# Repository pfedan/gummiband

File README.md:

# Gummiband

Gummiband is a topological ("rubber band") autorouter for KiCad. It plans every connection as a
topology first (which side of which pad, via or locked track it passes) and only then turns the
plan into geometry: tight any-angle tracks with real arcs, pulled taut around the obstacles like
rubber bands between the pins. The router is written in Rust, uses every core of your machine and
comes as a KiCad plugin, a command line tool and an MCP server for AI agents.

What you keep is yours: everything you lock in KiCad (power lanes, a converter layout from the
datasheet, critical pairs) stays untouched and the router works around it.

Status: early development. Results route almost everything on real boards but still need a KiCad
DRC pass and some hand finishing. See the [milestones](docs/MILESTONES.md).

## Requirements

- KiCad 9 or 10 board files. The plugin needs KiCad 10 with the IPC API enabled.
- A Rust toolchain (edition 2024, so Rust 1.85 or newer): <https://rustup.rs>.
- Optional: `kicad-cli` (ships with KiCad) for DRC runs from scripts and the MCP server,
  `rsvg-convert` (librsvg) and ImageMagick for renders and animations.

## Setup

Build the router once:

```bash
git clone https://github.com/pfedan/gummiband
cd gummiband
cargo build --release
# binary: target/release/gummiband
```

Then pick how you want to use it:

- **KiCad plugin** (recommended): link the `plugin/` folder into KiCad's IPC plugin directory,
  enable *Preferences > Plugins > Enable KiCad API*, and tell the plugin where the binary is
  (`plugin/settings.json`, copied from `settings.example.json`). Step by step in the
  [installation guide](docs/guide/installation.md).
- **Command line**: use `target/release/gummiband` directly, see below.
- **AI agents**: `cargo build --release -p gummiband-mcp` builds the MCP server, see
  [Working with an AI agent](docs/guide/ai-agents.md) and the reference in [docs/MCP.md](docs/MCP.md).

## Quickstart

### In KiCad

1. Optional, for a board whose parts are not placed yet: lock the connectors and whatever else
   has its spot, click *Place with Gummiband* and pick which parts move (new, not yet tested
   live in KiCad).
2. Lock the copper you want to keep (select, right click, *Locking > Lock*).
3. Click *Route with Gummiband* in the PCB editor's plugin toolbar.
4. Leave the defaults (keep locked copper, 14 runs, via cost 3.0, 3 geometry
   generations) and press OK. A window shows the phase, the generation, the routed connections,
   vias, length and remaining violations. The result keeps improving until you press *Accept
   current result*; the window tells you when the search has settled.
5. Look at the result. It arrives as one undo step, so Ctrl/Cmd+Z takes it back entirely.
6. Refill zones (B) and run the DRC. Fix or reroute what is left by hand, then save.

Your board file on disk is not touched until you save.

### On the command line

```bash
# what the router sees: layers, planes, nets, net classes, rules
target/release/gummiband info my_board.kicad_pcb

# optional: place the parts that are not locked or mechanical, into a new file
target/release/gummiband place my_board.kicad_pcb -o my_board.placed.kicad_pcb

# route it (or the placed file), keep locked tracks and vias, write a new file next to it
target/release/gummiband route my_board.kicad_pcb -o my_board.routed.kicad_pcb --scope keep_locked

# judge the result with KiCad
kicad-cli pcb drc --refill-zones --format json -o drc.json my_board.routed.kicad_pcb
```

The `.kicad_pro` (net classes) and `.kicad_dru` (custom rules) next to the board are read
automatically. Copy them next to the output before running the DRC on it.

## Documentation

The user guide lives in [docs/guide](docs/guide/README.md):

- [A tour of the features](docs/guide/tour.md): what Gummiband does, one picture per feature.
- [Installation](docs/guide/installation.md): binary, plugin, optional tools, troubleshooting.
- [Placing and routing in KiCad](docs/guide/kicad-plugin.md): the plugin dialogs and what each
  option does.
- [Command line](docs/guide/cli.md): every command and option, the output and the JSON report.
- [Working with an AI agent](docs/guide/ai-agents.md): setup of the MCP server and a session
  from netlist to DRC, with the power and reference plane checks.
- [Workflows](docs/guide/workflows.md): locking power lanes, routing by priority, judging results,
  placing parts, movable parts, placement variants, animations.
- [How Gummiband routes](docs/guide/concepts.md): what the router respects, how it decides, and
  what it does not do yet.
- [Benchmarks](docs/guide/benchmarks.md): the synthetic suite and the real boards.

Reference and development:

- [docs/MCP.md](docs/MCP.md): the MCP server for AI agents, tools and client setup.
- [docs/ARCHITECTURE.md](docs/ARCHITECTURE.md): crates, data model, algorithms.
- [docs/MILESTONES.md](docs/MILESTONES.md): what is done and what comes next.
- [docs/DECISIONS.md](docs/DECISIONS.md): standing decisions and working rules of the project.
- [docs/ENVIRONMENT.md](docs/ENVIRONMENT.md): the `GB_*` environment variables for development
  and measurements (logs, switches, experiment knobs); not a stable interface.
- [plugin/README.md](plugin/README.md): plugin internals, dry runs and tests.
- [bench/README.md](bench/README.md): the benchmark scripts.

## License

All rights reserved. Gummiband is not published under an open source license; ask the author
before using it beyond trying it out.

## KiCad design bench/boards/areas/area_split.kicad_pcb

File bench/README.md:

# Benchmarks

## Synthetic suite

`gen_boards.py` (plain Python 3) writes small KiCad 10 boards of increasing difficulty into
`boards/`, each as `<name>.kicad_pcb` plus `<name>.kicad_pro` (net classes, rules). The boards are
deterministic (fixed seeds, UUIDs derived from the board name); rerun the generator after changing
it and commit the boards together with it. Every unrouted board passes `kicad-cli pcb drc` with
only unconnected items.

| Board | Layers | What it tests |
| --- | --- | --- |
| `easy` | 2 | a few 2 pin connections between 0603 parts |
| `medium` | 2 | SOIC-14, SOT-23 and 0603 parts, random local netlist, an 8 pin GND net |
| `bus` | 2 | 16 bit bus between two 0.5 mm FPC connectors with a 90 degree turn, GND across the bus, 45 degree parts in the bend |
| `power_mix` | 2 | 1 mm (VIN, GND) and 0.75 mm (VOUT) nets with 0.2 mm signals through a 3.5 mm channel between two THT walls |
| `crossing` | 2 | two 1 mm pitch SMD connectors with reversed pin order |
| `qfn_fanout` | 4 (In1 GND, In2 3V3 planes) | QFN-48 at 0.5 mm to a ring of 40 pull resistors, plane fan-out vias |
| `four_signal_layers` | 4 signal | dense random netlist around two QFN-32 and two SOIC-14 |
| `bga_escape` | 4 (planes) | 8x8 BGA at 0.8 mm, 48 signals escape to four edge connectors, 0.1/0.1 mm rules |
| `bga_dense` | 4 (planes) | 10x10 BGA at 0.8 mm, 3 signal rings (84 signals): the inner ring needs vias on 2 signal layers |
| `fine_pitch` | 2 | QFN-56 at 0.4 mm with 0.2/0.19 mm rules, nets in pin order: a clean straight fan-out |
| `fine_pitch_mixed` | 2 | the same part with shuffled nets: vias and crossings right at the pins, the Corne problem in small |
| `diff_pairs` | 2 | 8 differential pairs (`_P`, `_N`) with a ground between them, 0.5 mm connectors at an angle, parts in the way |
| `matching` | 2 | a byte lane and a clock pair between two 0.5 mm connectors at an angle, with `length`, `skew` and `diff_pair_uncoupled` rules |
| `pair_wall` | 2 | a USB pair through the one gap of a wall of THT pins (the gap takes the wide pair or three single tracks, between the pins only one single track fits), six short nets across the wall next to the gap |
| `pair_traffic` | 2 | two long pairs from a connector to a QFN-32 across a field of 0603 parts with random local nets |
| `parts_easy` | 2 | part to part, level 1: QFN-32 and SPI flash with a planar bus, series resistors to a header |
| `parts_medium` | 2 | level 2: SPI flash in its real pinout (bus on both sides of the flash), I2C sensor with pull-ups and an interrupt, 6 bit bus with one swap, random local nets |
| `parts_hard` | 2 | level 3: QFN-48 with shared SPI to two devices, shared I2C with pull-ups to two more, 8 bit bus with two swaps to an edge connector, USB pair, random local nets |
| `parts_multi` | 4 (planes) | level 4: MCU (QFN-48) and PHY (QFN-32) with a 12 net bus with swaps, SPI flash, 6 bit latch bus, I2C shared by both chips with pull-ups, three pairs, a debug header wired to both, random local nets |
| `parts_multi_feed` | 4 (planes) | level 5: `parts_multi` with 40 scattered 0603 parts (chicken feed), half of them with a plane via |
| `parts_xhard` | 4 (planes) | extra hard: `parts_multi_feed` on a board 25 % smaller in each direction (positions scaled, edge connectors at their edge, overlaps spread apart) |

`run_suite.sh [board ...]` builds the CLI, routes every board into `boards/out/`
one board after another (`--runs 4 --generations 1 --geometry-generations 0` with `RAYON_NUM_THREADS=4`, override with
`RUNS`, `GENERATIONS`, `GEOMETRY_GENERATIONS`, `RAYON_NUM_THREADS`, `ROUTE_ARGS`, `TIMEOUT`), runs
`kicad-cli pcb drc --refill-zones` on each result (next to a copy of the board's `.kicad_pro`) and
prints a table: connections routed, vias, length, router wall time, Gummiband's own clearance
check, and the KiCad DRC counts (unconnected, clearance, shorts, crossings, other; silk and lib
types ignored). A crash or timeout on one board is reported in the table and the notes and does
not stop the suite. The table is also written to `boards/out/results.txt`; the router output of
each board is in `boards/out/<board>.route.log`.

## Route hashes (regression test)

`hashes.sh` routes the synthetic boards with fixed settings and prints one line per run: the name
and the SHA-1 of the routed `.kicad_pcb`. Runs without an open end are deterministic (same input
and seed, any thread count), so the list is a regression test: a refactoring or a
micro-optimisation must leave it unchanged. Only the router runs, no `kicad-cli` is needed.

The reference holds for every build. The router used to call `sin`, `cos`, `atan2`, `acos`, `exp`,
`log`, `pow` and `hypot` of the system's maths library, whose last bits differ between glibc
versions, musl and macOS: the first CI run (glibc of Ubuntu 26.04) changed 12 of 15 hashes of a
reference made with glibc 2.39, with the same compiler. Since 2026-11-10 these functions come from
`gummiband_core::math` (the `libm` crate, pure Rust, compiled in), and the binary asks the system's
maths library for nothing. Measured on x86_64 Linux: the glibc build and the static musl build give
the same hash on all 27 runs, where before they agreed on 6. The reference did not change with it:
the hashes are the ones the musl build had before. (The crate is a port of musl's maths library; its
`sin`, `cos`, `tan`, `atan2`, `acos` and `hypot` give the bits of today's musl, its `exp`, `ln` and
`powf` are an older version and differ in some last bits, which no run of the list noticed.) Another
processor (macOS on ARM) is expected to give the same hashes, because only operations that IEEE 754
fixes to the last bit are left to the hardware; that is not measured yet. `cargo test -p
gummiband-core math` compares the bits of every function with fixed numbers, on any machine.

```sh
cargo build --release -p gummiband-cli
bench/hashes.sh --check             # all boards against hashes.txt, about 2 min at 4 threads
QUICK=1 bench/hashes.sh --check     # the quick set against hashes.quick.txt, what CI runs

# two binaries against each other: the build before a change and the one after it, or two
# builds of the same source (glibc and musl, two compilers)
bench/hashes.sh --compare path/to/old/gummiband target/release/gummiband
QUICK=1 bench/hashes.sh --compare OLD NEW

bench/hashes.sh easy bus            # print the hashes of some boards, compare nothing
```

Every board is routed with `--runs 4 --generations 1 --geometry-generations 0 --no-move-parts`.
A few extra runs on small boards cover option paths the plain run does not touch (the defaults,
`--angles 45`, `--pairs band`, `--pairs pull`, `--patterns groups`, `--negotiate`); their names carry a
`+`, as in `medium+45`. `--check` prints a diff and exits with 1 when a hash differs, and a run
that fails shows up as `FAILED` in place of its hash. `RAYON_NUM_THREADS` sets the threads
(default 4) and changes the time only.

A change that is meant to alter results (a new heuristic, a changed default) is judged with
`compare.py` and the KiCad DRC as before, and then the reference is updated deliberately, in the
same commit as the change and with the reason in its message:

```sh
bench/hashes.sh --update            # rewrites hashes.txt
QUICK=1 bench/hashes.sh --update    # rewrites hashes.quick.txt
```

Never update the reference to make a refactoring pass: there a changed hash is a bug. A new board
from `gen_boards.py` needs `--update` too, since the full list covers every board in `boards/`.
The boards for areas in `boards/areas/` are in neither list, see below.

## Areas: pours and planes

`gen_boards.py` also writes five small boards into `boards/areas/`, each with one situation of a
pour or a plane. They are fixtures for the fill model behind `gummiband areas` (what the copper
fill of a net with a zone reaches), not routing problems: each routes in under a second.

| Board | Layers | What it holds | What the fill model says |
| --- | --- | --- | --- |
| `area_strips` | 2 | a GND pour on both layers (minimum width 0.2 mm, clearance 0.2 mm); six pens of locked track around one GND pad each, open only through a channel 4 mm long that leaves a strip of fill 0.10, 0.15, 0.20, 0.25, 0.30 or 0.40 mm wide | the pads behind 0.10 and 0.15 mm sit on islands (one via site each), the others are reached, as in KiCad; the pad behind 0.20 mm is doubtful |
| `area_island` | 2 | a GND pour on both layers; locked tracks from edge to edge cut the front into a region and a band with one GND pad each, strips of fill 0.21 mm wide between them that hold nothing, and the rest with a through hole pin; one GND pad stands in a pen of track that cuts its four spokes | the region and the band are islands with a via site each; the pad in the pen has no spoke; the strips are left out. Routed with `--areas fill --keep-locked`: two vias, one piece of track, all six pads reached (`area_route.rs`) |
| `area_halves` | 2 | GND parts at the left, GNDR parts at the right, three signals across, no zone; `area_halves.nets.json` leaves the two nets out of a route | a pour of both nets gives each a zone per layer around its own pads; no spot lies in two zones; all 6 pads of each are reached |
| `area_far` | 2 | VBUS with an area on B.Cu over the right third of the board, two through hole pins in it, six pins outside it | 2 of 8 pads reached; the farthest pad is 28.0 mm from a spot where a via lands in the area |
| `area_split` | 4 (In1 GND, In2 split) | In2.Cu holds +3V3 at the left and +5V at the right, 0.6 mm between the outlines; each net has one SMD pin over the other half and one through hole pin in it | each half reaches its two through hole pins; the pin in the other half lies outside the outline |

`cargo test -p gummiband-app --test area_boards` holds the model to the last column. The boards
are **not in the hash lists**: `hashes.sh` lists the boards of `boards/` only. They are quick
and their routed files are the same from run to run, but the hash of a routed file does not see
what they are for, the fill, and a board in the lists costs a reference line that every change
of the router has to carry.

`boards/areas/kicad/` holds four routed boards of the suite with a GND pour on both layers,
as KiCad 10 got them from the loop below (`<board>.s<seed>`). They are kept because the model
and KiCad disagreed on them; the tests in `area_boards.rs` pin KiCad's answer on each. They are
not written by `gen_boards.py` and must not be routed again: a new route is a new board that
KiCad has not seen.

### The model against KiCad's fill

The model was held against KiCad's fill on the planes of the LED controller, and against
KiCad 10 on the boards below (see "What KiCad 10 said"). To repeat it on a machine with
`kicad-cli` (KiCad 9 or 10) on the PATH:

```sh
python3 bench/gen_boards.py          # only if bench/boards/areas is missing
bench/areas-kicad.sh                 # the four boards above
```

and, for thin strips as a router leaves them, ten boards of the suite routed without GND, with
a pour of GND on both layers and one via per island:

```sh
for seed in 1 2 3; do
    POUR=GND:F.Cu,B.Cu \
    ROUTE_ARGS="--runs 4 --generations 1 --geometry-generations 0 --no-move-parts --seed $seed" \
    bench/areas-kicad.sh bench/boards/bus.kicad_pcb bench/boards/diff_pairs.kicad_pcb \
        bench/boards/fine_pitch.kicad_pcb bench/boards/fine_pitch_mixed.kicad_pcb \
        bench/boards/matching.kicad_pcb bench/boards/medium.kicad_pcb \
        bench/boards/parts_easy.kicad_pcb bench/boards/parts_hard.kicad_pcb \
        bench/boards/parts_medium.kicad_pcb bench/boards/power_mix.kicad_pcb
    cp bench/boards/out/areas/results.txt bench/boards/out/areas/results.seed$seed.txt
done
```

`areas-kicad.sh` routes a board (and pours it where asked), lets KiCad refill a copy
(`kicad-cli pcb drc --refill-zones --save-board`) and runs `gummiband areas --json` on that
copy, so that the model and KiCad's fill are compared on the same copper. It prints one line per
net and layer, also into `boards/out/areas/results.txt`:

- `mm2 model only / file only`: fill only one of the two has, beyond what the raster explains;
- `pads m/f`: pads only the model's fill touches, and pads only KiCad's fill touches;
- `unconn model/kicad`: the unconnected items the model expects for the net, and those KiCad's
  DRC counts;
- `doubtful`: the pads whose answer changes within one raster cell.

The model holds on a board where both pad lists are empty and the two unconnected counts agree.
A pad in `pads m/f` that is not in the doubtful list is a finding: send the line and the two
files `<name>.areas.json` and `<name>.filled/<name>.kicad_pcb`. On `area_halves` the question
is also whether KiCad reads the outlines as written (a region enclosed by another is cut into
its outline through a slit; this board has none, a board with an island of the other ground
has).

#### What KiCad 10 said

Measured 2026-11-11 with `kicad-cli` 10 and the commands above (the four area boards of that
day, the ten boards with seeds 1 to 3). Where the two disagreed the model now follows KiCad, and a test
pins KiCad's answer on the board where it showed:

| Where | The model said | KiCad 10 | Now |
| --- | --- | --- | --- |
| `area_strips` | the strip of 0.20 mm, the minimum width itself, is shut: 4 pieces on the front, 3 unconnected, `TP3.1` doubtful | passes it: 3 pieces, 2 unconnected | a cell centre at just the clearance is fill, the strip passes; `TP3.1` stays doubtful |
| `fine_pitch_mixed` seed 2, `R50.2` to `R54.2` and `R56.2` (a row at a pitch of 1.6 mm) | none of their spokes ends in fill: 7 unconnected | joins all six: 1 unconnected | a spoke also stays where it and a spoke of another pad hold each other's ends: 1 unconnected (`U1.57`) |
| `fine_pitch_mixed` seed 3, `U1.57` (exposed pad) | an island, 1 piece of fill on the front | unconnected too, but 2 pieces | the spokes are laid and tested as KiCad lays them: the island is a piece of 1 mm2 that stays, 2 pieces |
| `matching` seed 3, `J1.16` | no spoke ends in fill, and not doubtful | joins it | still not reached, but doubtful: the end of its one free spoke lies 0.05 mm from the clearance of a track, one cell outside the fill at the raster as it is, inside with half a cell less |
| `parts_medium` (all seeds), `fine_pitch_mixed` seeds 1 and 3, back layer | nothing of GND holds the pour there: every piece left out, 0 mm2 | keeps all of it (1393 to 1760 mm2 in 1 or 35 to 41 pieces) and warns of isolated copper for each | the pieces stay in the model and the report says so (`isolated`). `ground_pour` and `pour_stitch` still write the zone of such a layer: not writing it is open |
| `parts_medium`, `U2.4` | reached, doubtful | unconnected | as before: this is what doubtful is for |
| `area_halves`, `area_far`, `area_split` | | no difference at any pad, no DRC item; the model has 0.4 to 5 mm2 more fill of 344 to 1375 | as before |

What is assumed about KiCad's filler and not measured case by case: the end of a spoke lies the
thermal gap, half the minimum width and 0.005 mm beyond the box of the pad; a spoke is as wide
as the spoke width or the short side of the pad and is left out where that is under the minimum
width; it stays when its end lies in the fill as it is after the minimum width took its part,
or when it and a spoke of another pad hold each other's ends; other copper then cuts it by its
clearance. A pad whose answer hangs on this within a raster cell is named as doubtful.

On `J1.16` the two are not reconciled. Read from the copper, its spoke ends in a pocket of fill
of about 0.2 mm2 between the tracks of DQ4 and DQ0, which lie 0.16 mm apart where the pocket
would have to open: the pad would hang on that pocket and on nothing else. If KiCad calls the
pad connected, something in this reading is wrong; the filled board at 105.5, 114.7 shows what.

### `areas tracks` against `areas fill`

`areas-route.py` routes a board both ways with the same binary, `--areas tracks` (a net with a
pour is laid as tracks) and `--areas fill` (the other nets first, then only what the fill does
not reach), and prints one line per board, seed and mode: connections, the pads of the area
nets that the router's fill model leaves open on the routed board with its pour, the pieces
and spots of the own clearance check, vias, length, CPU seconds, and the seconds the fill model
took inside the search (summed over the threads) with the number of its runs. It needs no KiCad:

```sh
cargo build --release -p gummiband-cli
bench/areas-route.py                 # ten boards of the suite with GND poured, the four area boards
bench/areas-route.py /path/to/board.kicad_pcb=GND      # another board, GND poured on F.Cu and B.Cu
bench/areas-route.py /path/to/board.kicad_pcb          # the zones of the file are the areas
```

The table is also written to `boards/out/areas-route/results.txt` (and `results.json`); the
routed boards are deleted unless `--keep` is given. `--fill-args=--no-area-stitch` routes the
fill runs without the vias for islands, and `GB_AREA_ESCAPE=0` in the environment without the
price at the pads of the area nets.
`--modes fill` routes one mode only. Write `--args=...` and `--fill-args=...` with the equals
sign: their values begin with a dash.

Measured without KiCad (2026-11-14, commit 5d63666 of `claude/geometry`, the settings of the
suite: `--runs 4 --generations 1 --geometry-generations 1 --no-move-parts`). Every number is
the sum of the seeds 1, 2 and 3; `open pads` is the router's own model, not KiCad.

| board | mode | routed | open pads | pieces/spots | vias | of them island vias | mm | cpu s | model s (runs) |
| --- | --- | ---: | ---: | ---: | ---: | ---: | ---: | ---: | ---: |
| `bus` | tracks | 66/66 | 0 | 0/0 | 60 | 0 | 1911 | 41 |  |
| `bus` | fill | 66/66 | 0 | 0/0 | 50 | 8 | 1933 | 43 | 7 (27) |
| `diff_pairs` | tracks | 93/93 | 0 | 0/0 | 90 | 0 | 2916 | 53 |  |
| `diff_pairs` | fill | 93/93 | 0 | 2/2 | 126 | 0 | 2925 | 96 | 11 (36) |
| `fine_pitch` | tracks | 336/336 | 0 | 0/0 | 6 | 0 | 2304 | 18 |  |
| `fine_pitch` | fill | 336/336 | 0 | 0/0 | 6 | 6 | 1928 | 29 | 6 (24) |
| `fine_pitch_mixed` | tracks | 336/336 | 0 | 28/5 | 368 | 0 | 4509 | 393 |  |
| `fine_pitch_mixed` | fill | 335/336 | 0 | 1/1 | 426 | 0 | 4211 | 624 | 44 (157) |
| `matching` | tracks | 78/78 | 0 | 0/0 | 102 | 0 | 1800 | 66 |  |
| `matching` | fill | 78/78 | 0 | 0/0 | 18 | 6 | 1572 | 191 | 8 (27) |
| `medium` | tracks | 114/114 | 0 | 0/0 | 36 | 0 | 1347 | 7 |  |
| `medium` | fill | 114/114 | 0 | 0/0 | 42 | 6 | 1137 | 15 | 6 (27) |
| `parts_easy` | tracks | 66/66 | 0 | 0/0 | 15 | 0 | 450 | 2 |  |
| `parts_easy` | fill | 66/66 | 0 | 0/0 | 3 | 0 | 393 | 8 | 4 (27) |
| `parts_hard` | tracks | 225/225 | 0 | 0/0 | 172 | 0 | 3260 | 16 |  |
| `parts_hard` | fill | 225/225 | 0 | 0/0 | 162 | 18 | 2802 | 45 | 13 (27) |
| `parts_medium` | tracks | 129/129 | 0 | 0/0 | 60 | 0 | 1545 | 9 |  |
| `parts_medium` | fill | 129/129 | 0 | 0/0 | 27 | 0 | 1560 | 21 | 10 (27) |
| `power_mix` | tracks | 57/57 | 0 | 0/0 | 17 | 0 | 960 | 7 |  |
| `power_mix` | fill | 57/57 | 0 | 0/0 | 15 | 0 | 657 | 12 | 8 (27) |
| **the ten** | tracks | 1500/1500 | 0 | 28/5 | 926 | 0 | 21002 | 612 |  |
| **the ten** | fill | 1499/1500 | 0 | 3/3 | 875 | 44 | 19118 | 1083 | 116 (406) |
| `area_strips` | tracks | 27/27 | 0 | 0/0 | 0 | 0 | 189 | 1 |  |
| `area_strips` | fill | 27/27 | 0 | 0/0 | 0 | 0 | 0 | 3 | 3 (24) |
| `area_far` | tracks | 60/60 | 0 | 0/0 | 0 | 0 | 654 | 2 |  |
| `area_far` | fill | 60/60 | 0 | 0/0 | 6 | 0 | 549 | 6 | 4 (27) |
| `area_split` | tracks | 51/51 | 0 | 0/0 | 36 | 0 | 399 | 2 |  |
| `area_split` | fill | 51/51 | 0 | 0/0 | 36 | 0 | 399 | 2 | 0 (0) |
| `area_halves` | tracks | 69/69 | 0 | 0/0 | 3 | 0 | 678 | 3 |  |
| `area_halves` | fill | 69/69 | 0 | 0/0 | 6 | 0 | 468 | 17 | 10 (27) |
| ledctl, its planes | tracks | 1042/1044 | 0 | 26/11 | 934 | 0 | 7366 | 363 |  |
| ledctl, its planes | fill | 1042/1044 | 0 | 26/11 | 934 | 0 | 7366 | 368 | 0 (0) |
| ledctl, GND poured | tracks | 1042/1044 | 0 | 26/11 | 934 | 0 | 7366 | 369 |  |
| ledctl, GND poured | fill | 1098/1098 | 0 | 3/3 | 945 | 8 | 8194 | 335 | 130 (56) |

In short, on the ten: `fill` lays 9 % less track and 6 % fewer vias than `tracks`, joins as
much (one connection of `fine_pitch_mixed` is lost to a short the last check takes out) and
takes 77 % more CPU time. The table of 2026-11-11 (commit 980246a) had 1047 vias for `tracks`
and 815 for `fill`: since then the routes of `tracks` got better by more vias than those of
`fill`.

What the table does not show:

- The two open connections of the LED controller with `tracks` are `BUCK_PG from R116.2` on
  the seeds 1 and 3: the small search of the suite settings leaves it open, the default
  settings of a route join it on every seed.
- On more seeds `fill` has open pads on `diff_pairs`: 3 on seed 4 and 2 on seed 7 (seeds 4 to
  7 measured on `fine_pitch_mixed`, `diff_pairs`, `bus` and `parts_hard`). GND has four pads
  there, the fill lies in 38 pieces, and the pads at the ends of the connectors have every
  spoke of their thermal relief cut and find no way to the piece that counts as the area. The
  step that lays open connections again on the finished copper does not help them.
- The three bullets below are of 2026-11-11 (commit 980246a) and were not measured again.
  At that commit the two open pads of the table were `J1.16` and `J2.16` of `matching` on
  seed 1 (pads with a thermal relief whose spokes end in no fill on the finished copper);
  `matching` joins everything now.
- A second run of the 42 lines with `fill` gave the same 42 lines.
- Without the vias for islands (`--fill-args=--no-area-stitch`, the ten boards): 18 open pads
  in 12 groups on 13 of the 30 runs, 877 vias, 19291 mm. Looked at on `parts_hard`: the
  search ended the track of `C2.2` in a piece of fill that hung on the area then and is an
  island on the finished copper; the last check takes such a track back. The via for an
  island is set on the finished copper and does not depend on what the search saw. This
  reading is in doubt since: the last check could also take a track back because it did not
  know the cells of the area (see `area_island`), which gives the same picture. Not measured
  again after that repair.
- Without the price at the pads (`GB_AREA_ESCAPE=0`, the ten boards): 13 open pads on 3 of the
  30 runs (`fine_pitch_mixed` 12, `diff_pairs` 1), 110 violating pieces at 24 spots against 6
  at 6, 780 vias, 19022 mm.
- The LED controller as it is has its planes on inner layers and no area on a routed layer:
  the files of `tracks` and `fill` are the same byte for byte. With GND poured on the outer
  layers as well (`ledctl.kicad_pcb=GND`) the route with `fill` counts 366 connections against
  348, because every group of pads of an area net counts and not only the pads that need a
  way to the plane.
- `model s` is wall time summed over the threads of the search. The machine was shared with
  another job, so it is an upper bound on the CPU time of the model.

**With KiCad** (`kicad-cli` of KiCad 9 or 10 on the PATH), `--kicad` lays the pour on every
result (the example `pour_stitch`: the zones, and one via per island that still has none), lets
KiCad refill it and adds three columns from KiCad's DRC: unconnected items (of the area nets /
of all nets), clearance violations, dangling vias and track ends. This is the judgement that
counts; the model's column `open pads` is what the router believed.

```sh
cargo build --release -p gummiband-cli --example pour_stitch
bench/areas-route.py --kicad --keep                    # the fourteen boards, three seeds each
```

The acceptance run on the Corne (`prepare-ext.sh` fetches and strips it into
`work/ext/corne/`), with the default settings of a route, three seeds:

```sh
bench/prepare-ext.sh
cargo build --release -p gummiband-cli --example pour_stitch
bench/areas-route.py --kicad --keep --args="" bench/work/ext/corne/corne.kicad_pcb=GND
```

`areas fill` passes when, on every seed and against the line of `tracks` ("route all, then
pour"): `unconn` of GND is 0; `clear` is no more than the 119 that the Corne had with GND left
out of the route; `vias` is no more than the 226 of that run plus the vias set for islands
(`areas: N vias set for islands of fill` in the log, `area_vias` in the report); `dangling` is
0. For the LED controller with a GND pour on the outer layers
(`bench/areas-route.py --kicad --keep --args="" /path/to/ledctl.kicad_pcb=GND`) nothing may be
worse than its line of `tracks`. With `--keep` the boards KiCad judged are
`boards/out/areas-route/<board>.s<seed>.<mode>.filled.kicad_pcb`, next to `.drc.json`; send
those two files for a pad that KiCad's DRC calls unconnected and the column `open pads` does
not count.

On the Corne with KiCad 10 (2026-11-11, before the two repairs named above) `fill` had more
clearance violations than `tracks` on every seed (573 against 439 over the seeds 1 to 3), most
of them at the two QFNs. Whether the price at the pads of the area nets pushes the signals
aside there is measured with the same seeds and the price off:

```sh
bench/areas-route.py --kicad --keep --modes fill --args="" bench/work/ext/corne/corne.kicad_pcb=GND
GB_AREA_ESCAPE=0 bench/areas-route.py --kicad --keep --modes fill --args="" bench/work/ext/corne/corne.kicad_pcb=GND
```

Compare `clear`, `unconn` and `vias` of the two tables line by line (the second run overwrites
`boards/out/areas-route/results.txt`: copy it first). Without KiCad the column `pieces/spots`
of the own clearance check stands in for `clear`. The price is not to be tuned on the small
boards alone: of the ten only `fine_pitch_mixed` and `diff_pairs` answer to it (see above). One
route of the Corne with the default settings takes more than an hour of CPU time.

## Two sided placement

`gen_two_sided.py` writes four synthetic boards into `boards/two_sided/` for `gummiband place
--two-sided` (placement only, no routing): `ts_som` (4 layers, 42 x 30 mm, BGA SoC and memory,
PMIC, about 120 0402 parts, a board to board connector locked on the back; the parts need about
1.4 times the front), `ts_sensor` (34 x 23 mm, a coin cell holder locked on the back, an antenna
keepout on the front: one sided nothing fits, two sided the front holds nearly all), `ts_roomy` (a
control with room to spare) and `ts_tht` (through hole electrolytics and a terminal block between
SMD converters). `check_sides.py PLACED [--input ORIGINAL]` checks a result from the file alone:
courtyard overlaps per side, the holes of through hole parts against parts on the other side, SMD
pads and courtyards on the layers of their side, mirrored texts on the back, and with `--input`
that every part that changed sides keeps its pad distances and is mirrored. `draw_sides.py PLACED
OUT.svg` draws front and back next to each other.

With `--iters 1000000`, one start, seed 1 (counts of 2026-11-10, with the maths of
`gummiband_core::math`; the system's maths gave 0 and 10 on `ts_sensor` and `ts_tht`):

| Board | One sided | Two sided: parts on the back | Wall time |
| --- | --- | --- | --- |
| `ts_som` | fails before the search, 321 mm2 missing | 105 | 20 s |
| `ts_sensor` | fails before the search, 275 mm2 missing | 1 (the front holds the rest once the holder only takes the back) | 6 s |
| `ts_roomy` | places | 9 (decoupling capacitors under their IC) | 3 s |
| `ts_tht` | places | 11, some under the electrolytics | 3 s |

`check_sides.py` finds no problem on any of them.

## LED controller

`prepare-ledctl.sh` strips the real LED controller board,
`run-ledctl.sh` routes it and prints the KiCad DRC summary; `drc_report.py` summarizes a
DRC JSON report in more detail.

## Relaxation on the CPU and the GPU

`cargo run --release -p gummiband-cli --features gpu --example relax_bench -- BOARD` routes the
board with a small search and relaxes the same routing on the CPU and the GPU. It prints the time,
the core seconds, a breakdown per round, the violations and a hash of the result. `--ensemble N`
relaxes it N times with a margin changed by next to nothing: the relaxation is chaotic, a single
violation count says little. Compare core seconds when other jobs run on the machine.

## Profiling

`GB_LOG=timing` prints cumulative phase timers of a route (search, relaxation rounds, taut, check;
parallel calls add up, so the shares are of the work, not of the clock). For the functions
behind them, record with [samply](https://github.com/mstange/samply) (`cargo install samply`;
Instruments needs a full Xcode) and summarise with `profile.py`:

```sh
samply record --save-only --unstable-presymbolicate -r 1000 -o run.json.gz -- \
    target/release/gummiband route BOARD -o out.kicad_pcb
bench/profile.py run.json.gz parts      # busy time by part: search, relaxation, taut, check ...
bench/profile.py run.json.gz top 40     # self and total time per function
bench/profile.py run.json.gz lines 'relax_while::\{closure#41\}' relax.rs target/release/gummiband
```

A speed change that should not change results is checked by the SHA-1 of the routed file: the
result of a route is the same for any number of threads.

## Real boards (external)

`kicad-autorouter-benchmarks.zip` (not in the repository; sources and licenses in its
`QUELLEN.md`) holds four fully routed open hardware boards. `prepare-ext.sh [zip]` unpacks it
into `work/ext/src/` and strips every track, via and pour outside the plane layers into
`work/ext/<name>/`; the plane layers are marked as KiCad `power` layers in the stripped file, so
the board describes itself. `run-ext.sh NAME [route args]` routes one board into
`work/ext/routed/NAME/` and prints the KiCad DRC summary.

| Name | Board | Routing layers | Planes kept | Notes |
| --- | --- | --- | --- | --- |
| `corne` | Corne Cherry hotswap (panel of two halves) | F, B | none | Edge.Cuts with mouse bites and T joints: the outline falls back to the bounding box with the edge lines as obstacles; GND is routed as a net |
| `arty` | Arty MPW Tester | F, B | In1 (GND), In2 (split power) | cut-out in the middle, copper logos |
| `ulx3s` | ULX3S (ECP5 BGA 381, 0.8 mm) | F, B | In1 (split power), In2 (GND) | the original also routes on In2 |
| `jetson` | Jetson Orin baseboard | F, In3, In5, B | In1, In2, In4, In6 | 1927 connections, diff pairs, custom rules |

First results (2026-10-29, `--runs 14 --generations 1`, no geometry generations):

| Board | Routed | Vias | Time | Main problems |
| --- | --- | --- | --- | --- |
| `arty` | 322/323 | 179 | 10 s | two tracks on top of each other along the left edge, FTDI area |
| `corne` | 471/482 | 453 | 136 s | the two RP2040 fan-outs (0.4 mm pitch) |
| `ulx3s` | 651/796 | 377 | 304 s | BGA escape on two signal layers, bundles along the board edge |

## DDR5 testbed (length matching)

`prepare-ddr5.sh` fetches Antmicro's DDR5 testbed (Apache-2.0, pinned to one commit) into
`work/ddr5/src/`, writes the board with its routing and the real layer types into
`work/ddr5/reference/` and the stripped board into `work/ddr5/ddr5/`. `ddr5-testbed.kicad_dru`
holds the length rules (the board has none of its own). `run-ddr5.sh [route args]` prints the
lengths of the reference routing, routes the stripped board into `work/ddr5/routed/`, prints its
lengths and the KiCad DRC summary.

## Repository housekeeping

`merged-branches.sh [REMOTE] [MAIN]` lists the branches of the remote (default `origin`) whose
head is an ancestor of its main branch, and prints the `git push origin --delete ...` command for
them. It is read-only: it asks the remote for its heads, fetches nothing and deletes nothing. A
head whose commit is not in the local clone is listed as unknown, never as merged.

## Geometry test stand

`geostand/` holds small boards with one basic situation each, where the right copper is known:
one track around a via, a round pad or a corner; one to three tracks between two pads, a pad and a
via, two vias; a row of pads at 0.4 and 0.5 mm whose tracks turn hard behind the pads; bundles of
three and six around a corner; a turn with a neighbour on the inside; a tangent from via to via; a
track and a via next to a cutout of the board; a via between two pads and between two rows of
pads; a pad with a clearance of its own. Rules: clearance 0.2 mm, track 0.2 mm.

Every case comes in five forms, named by the room its channel has beyond what the copper needs:
`loose` (0.3 mm), `tight20` (20 um), `tight` (5 um), `exact` (none: the copper fits to the
micrometre, as boards are often laid out) and `short` (10 um missing: the right answer is "does
not fit"). `gen_geostand.py DIR` writes the 130 boards, and for each a reference solution
(`.ref.kicad_pcb`), the copper as it should be, with the spare room shared between the gaps.
The boards are not in the repository; the generator writes them in a second.

- `check_refs.py DIR` (needs `kicad-cli`) runs KiCad's DRC on the unrouted boards and on the
  references: clean and connected for every form but `short`, at least one entry there. A case
  whose reference fails does not measure what it claims. KiCad 10.0.7 passes 130 of 130.
- `run_geostand.py ROUTER DIR OUT` routes every board (`--seed 1 --no-move-parts`) and judges it
  with KiCad's DRC (`--all-track-errors`, every kind that concerns copper, counted by place);
  `table.py OUT` prints the table.
- `run_own.py ROUTER DIR OUT` does the same with the router's own check and needs no KiCad. On the
  130 boards the two agree: the own check is clean exactly where KiCad reports no place.
- `check.sh [--update] [ROUTER]` generates, routes and compares routed connections and spots per
  board with `expected.txt`: the stand as a regression test (about five minutes on four cores).
- `probe.py ROUTER CASE [slack in um ...]` builds one case with each slack and says from which
  slack on the router lays it (it honours the `GB_` variables of the shell, and writes into
  `probe/` in the current directory).

A board is right if it is fully routed and clean, or for `short` clean and not fully routed.
`expected.txt` records where the router stands, not where it should be: 47 of 130 are right at
the time of writing. A change that moves a board is meant to show up in that file.

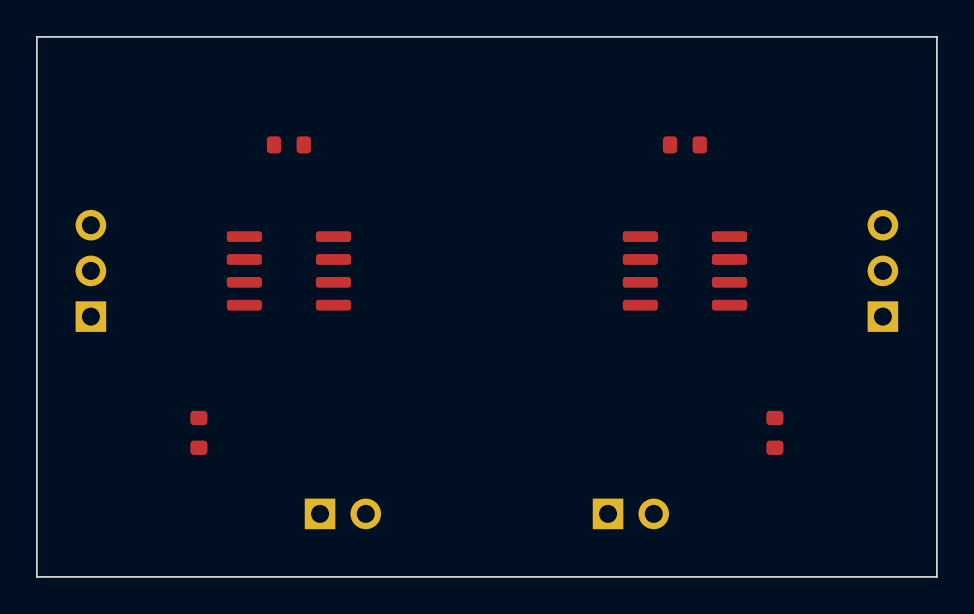
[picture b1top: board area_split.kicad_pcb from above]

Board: 4 copper layers, 50.0 x 30.0 mm, 10 parts (0 on the bottom side), 8 nets, no tracks yet.

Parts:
C1, C2: 100n; C_0603
J1, J2: Conn; PinHeader_1x03
J3, J4: Conn; PinHeader_1x02
R1, R2: 10k; R_0603
U1, U2: IC; SOIC-8

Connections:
+3V3: C1.1, J1.1, J1.3, J4.2, R2.1, U1.8
+5V: C2.1, J2.1, J2.3, J3.1, R1.1, U2.8
GND: C1.2, C2.2, J1.2, J2.2, J3.2, J4.1, U1.4, U2.4
P1: R1.2, U1.1
P2: R2.2, U2.5
X1: U1.7, U2.1
X2: U1.6, U2.2
X3: U1.5, U2.3

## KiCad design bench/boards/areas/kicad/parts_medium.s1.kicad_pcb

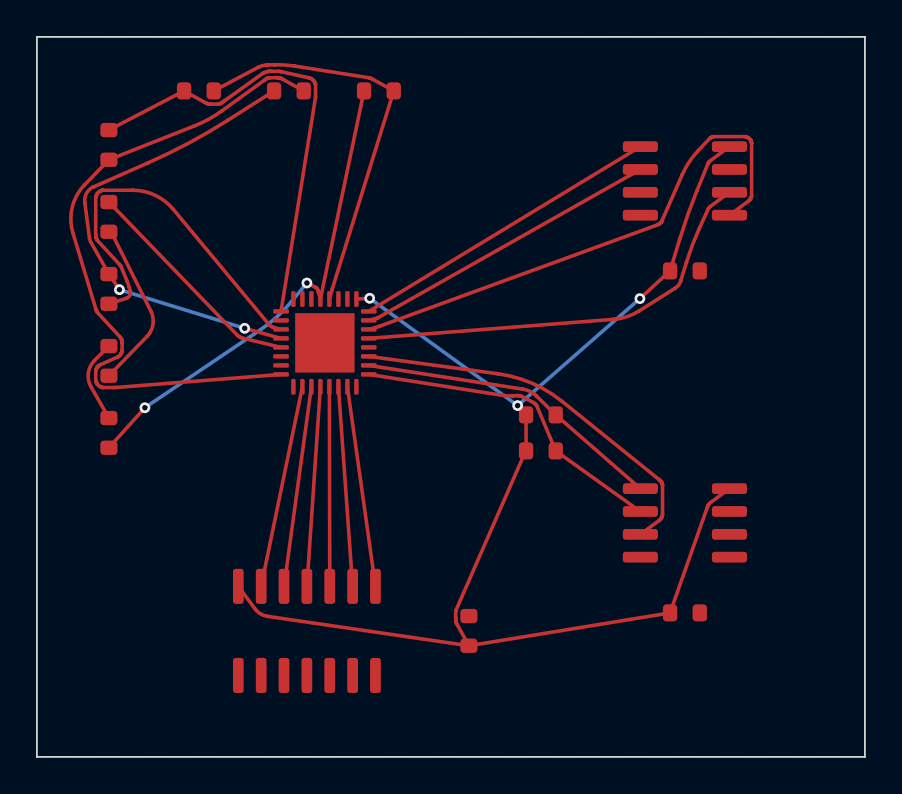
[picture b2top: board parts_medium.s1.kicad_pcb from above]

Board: 2 copper layers, 46.0 x 40.0 mm, 17 parts (0 on the bottom side), 24 nets.

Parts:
C1, C2, C3: 100n; C_0603
R1, R2: 4k7; R_0603
R3, R4, R5, R6, R7, R8, R9, R10: 10k; R_0603
U1: MCU; QFN-32
U2: Flash; SOIC-8
U3: Sensor; SOIC-8
U4: Latch; SOIC-14

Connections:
+3V3: C1.1, C2.1, C3.1, R1.1, R2.1, U1.25, U2.8, U3.8, U4.14
CS: U1.24, U2.1
GND: C1.2, C2.2, C3.2, U1.33, U2.4, U3.4, U4.7
INT: U1.19, U3.3
MISO: U1.23, U2.2
MOSI: U1.22, U2.5
N1: R5.1, U1.3
N2: R4.1, R6.1
N3: R6.2, R7.2
N4: R5.2, R9.1, U1.4
N5: R3.1, R9.2, U1.8
N6: R8.2, R10.2, U1.28
N7: R4.2, U1.5
N8: R3.2, R8.1, U1.1
N9: R7.1, R10.1, U1.29
Q0: U1.10, U4.13
Q1: U1.11, U4.12
Q2: U1.13, U4.10
Q3: U1.12, U4.11
Q4: U1.14, U4.9
Q5: U1.15, U4.8
SCK: U1.21, U2.6
SCL: R2.2, U1.17, U3.2
SDA: R1.2, U1.18, U3.1

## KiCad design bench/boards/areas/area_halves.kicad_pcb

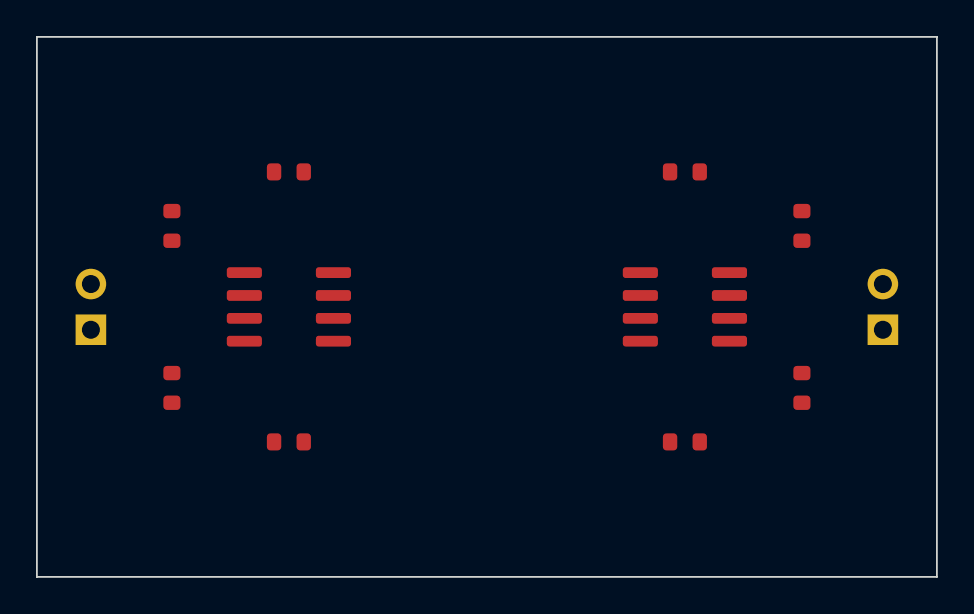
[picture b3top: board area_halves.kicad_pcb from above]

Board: 2 copper layers, 50.0 x 30.0 mm, 12 parts (0 on the bottom side), 11 nets, no tracks yet.

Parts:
C1, C2, C3, C4: 100n; C_0603
J1, J2: Conn; PinHeader_1x02
R1, R2, R3, R4: 10k; R_0603
U1, U2: IC; SOIC-8

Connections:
GND: C1.2, C2.2, J1.2, R1.2, R2.2, U1.4
GNDR: C3.2, C4.2, J2.2, R3.2, R4.2, U2.4
P1: R1.1, U1.1
P2: R2.1, U1.2
P3: R3.1, U2.6
P4: R4.1, U2.5
VCC: C1.1, C2.1, J1.1, U1.8
VCCR: C3.1, C4.1, J2.1, U2.8
X1: U1.7, U2.1
X2: U1.6, U2.2
X3: U1.5, U2.3

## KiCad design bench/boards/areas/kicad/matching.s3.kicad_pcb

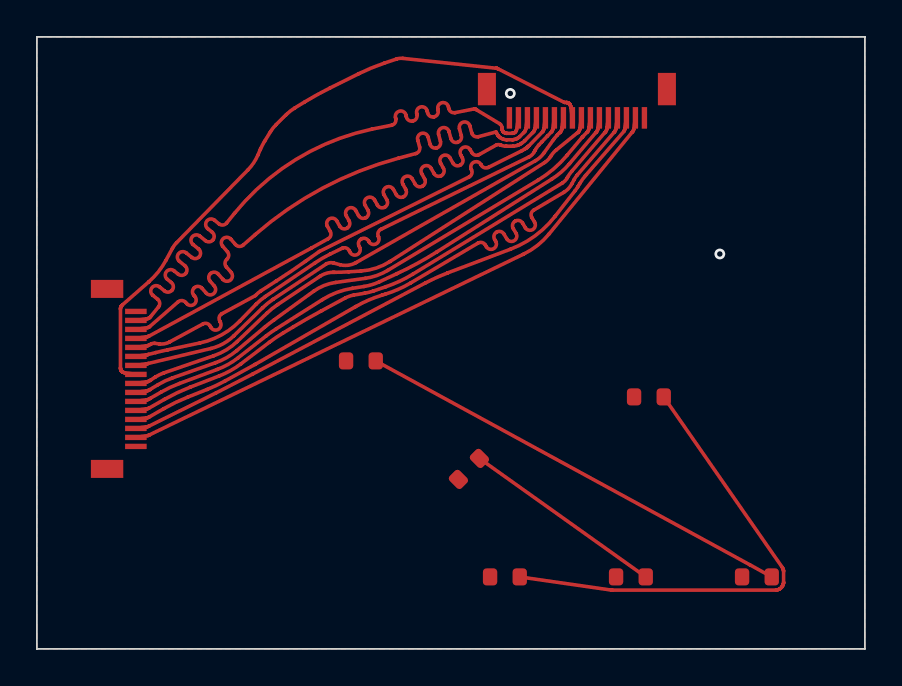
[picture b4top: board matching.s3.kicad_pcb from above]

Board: 2 copper layers, 46.0 x 34.0 mm, 8 parts (0 on the bottom side), 18 nets.

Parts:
C1, C2, C3, C4, C5, C6: 100n; C_0603
J1, J2: FPC; FPC-16P-0.5mm

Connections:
CLK_N: J1.3, J2.14
CLK_P: J1.4, J2.13
DQ0: J1.15, J2.2
DQ1: J1.14, J2.3
DQ2: J1.13, J2.4
DQ3: J1.12, J2.5
DQ4: J1.9, J2.8
DQ5: J1.8, J2.9
DQ6: J1.7, J2.10
DQ7: J1.6, J2.11
DQS_N: J1.10, J2.7
DQS_P: J1.11, J2.6
G1: J1.5, J2.12
G2: J1.2, J2.15
GND: C1.1, C2.1, C3.1, C4.1, C5.1, C6.1, J1.1, J1.16, J2.1, J2.16
V1: C1.2, C4.2
V2: C2.2, C5.2
V3: C3.2, C6.2

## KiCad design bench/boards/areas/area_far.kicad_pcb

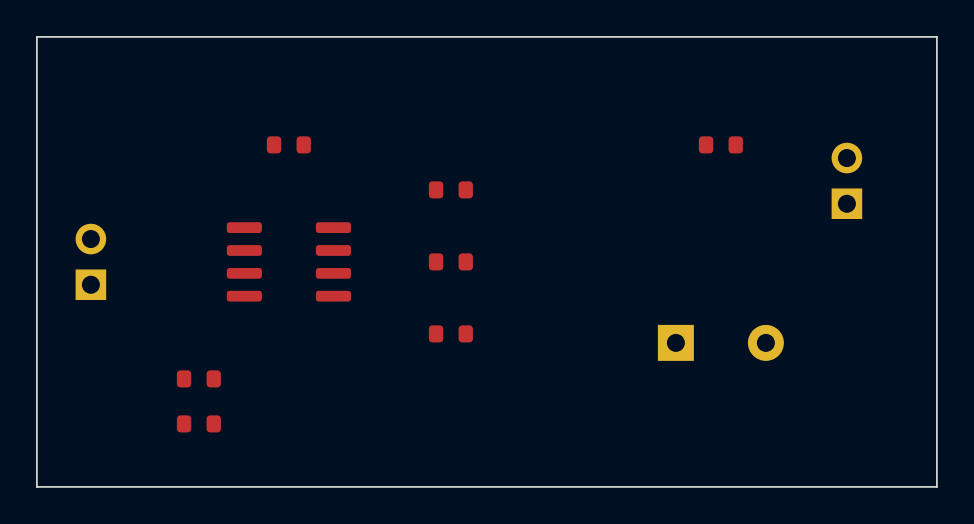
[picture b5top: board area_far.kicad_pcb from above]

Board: 2 copper layers, 50.0 x 25.0 mm, 11 parts (0 on the bottom side), 7 nets, no tracks yet.

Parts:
C1, C3: 100n; C_0603
C2: 470u; CP_Radial_D8.0mm_P5.00mm
J1, J2: Conn; PinHeader_1x02
R1, R2, R3, R4, R5: 10k; R_0603
U1: IC; SOIC-8

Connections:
GND: C1.1, C2.2, C3.2, J1.2, J2.2, R1.2, R2.2, R3.2, U1.4
S1: R1.1, U1.7
S2: R2.1, U1.6
S3: R3.1, U1.5
T1: R4.1, U1.1
T2: R5.1, U1.2
VBUS: C1.2, C2.1, C3.1, J1.1, J2.1, R4.2, R5.2, U1.8

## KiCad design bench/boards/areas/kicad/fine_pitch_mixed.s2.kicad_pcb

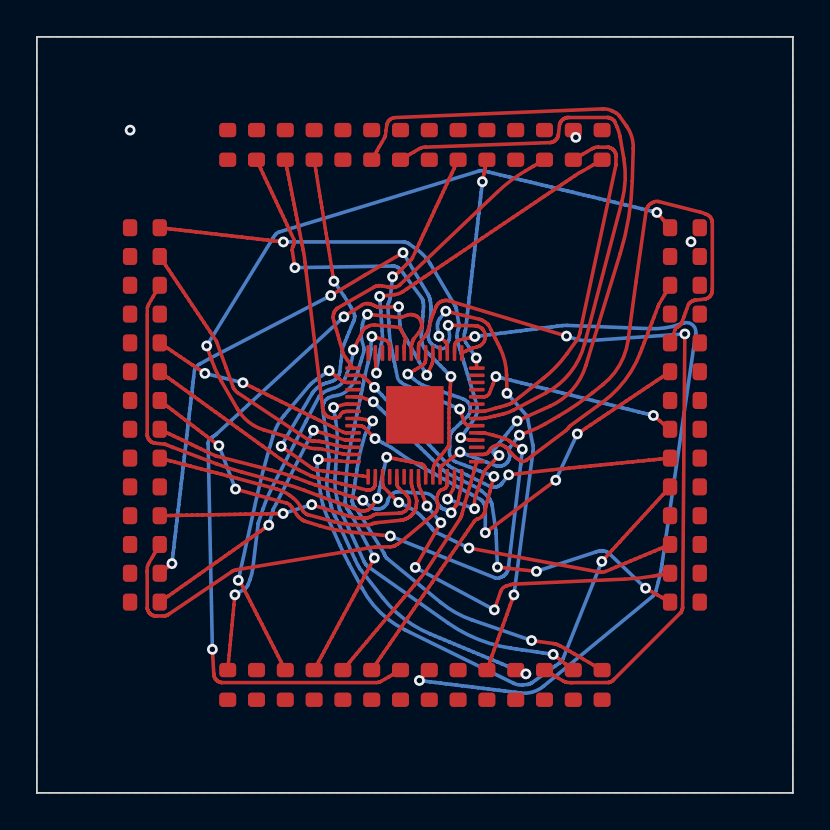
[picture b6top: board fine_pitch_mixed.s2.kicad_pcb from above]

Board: 2 copper layers, 42.0 x 42.0 mm, 57 parts (0 on the bottom side), 57 nets.

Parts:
R1, R2, R3, R4, R5, R6, R7, R8, R9, R10, R11, R12, R13, R14, R15, R16, R17, R18, R19, R20, R21, R22, R23, R24, R25, R26, R27, R28, R29, R30, R31, R32, R33, R34, R35, R36, R37, R38, R39, R40, R41, R42, R43, R44, R45, R46, R47, R48, R49, R50, R51, R52, R53, R54, R55, R56: 10k; R_0603
U1: MCU; QFN-56

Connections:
F1: R1.1, U1.32
F2: R2.1, U1.12
F3: R3.1, U1.23
F4: R4.1, U1.54
F5: R5.1, U1.10
F6: R6.1, U1.16
F7: R7.1, U1.33
F8: R8.1, U1.28
F9: R9.1, U1.21
F10: R10.1, U1.56
F11: R11.1, U1.19
F12: R12.1, U1.26
F13: R13.1, U1.43
F14: R14.1, U1.11
F15: R15.1, U1.51
F16: R16.1, U1.41
F17: R17.1, U1.3
F18: R18.1, U1.53
F19: R19.1, U1.29
F20: R20.1, U1.48
F21: R21.1, U1.47
F22: R22.1, U1.44
F23: R23.1, U1.18
F24: R24.1, U1.45
F25: R25.1, U1.50
F26: R26.1, U1.49
F27: R27.1, U1.6
F28: R28.1, U1.8
F29: R29.1, U1.13
F30: R30.1, U1.52
F31: R31.1, U1.30
F32: R32.1, U1.39
F33: R33.1, U1.25
F34: R34.1, U1.9
F35: R35.1, U1.4
F36: R36.1, U1.38
F37: R37.1, U1.2
F38: R38.1, U1.14
F39: R39.1, U1.37
F40: R40.1, U1.17
F41: R41.1, U1.22
F42: R42.1, U1.5
F43: R43.1, U1.40
F44: R44.1, U1.24
F45: R45.1, U1.7
F46: R46.1, U1.15
F47: R47.1, U1.46
F48: R48.1, U1.27
F49: R49.1, U1.35
F50: R50.1, U1.20
F51: R51.1, U1.34
F52: R52.1, U1.42
F53: R53.1, U1.31
F54: R54.1, U1.1
F55: R55.1, U1.36
F56: R56.1, U1.55
GND: R1.2, R2.2, R3.2, R4.2, R5.2, R6.2, R7.2, R8.2, R9.2, R10.2, R11.2, R12.2, R13.2, R14.2, R15.2, R16.2, R17.2, R18.2, R19.2, R20.2, R21.2, R22.2, R23.2, R24.2, R25.2, R26.2, R27.2, R28.2, R29.2, R30.2, R31.2, R32.2, R33.2, R34.2, R35.2, R36.2, R37.2, R38.2, R39.2, R40.2, R41.2, R42.2, R43.2, R44.2, R45.2, R46.2, R47.2, R48.2, R49.2, R50.2, R51.2, R52.2, R53.2, R54.2, R55.2, R56.2, U1.57

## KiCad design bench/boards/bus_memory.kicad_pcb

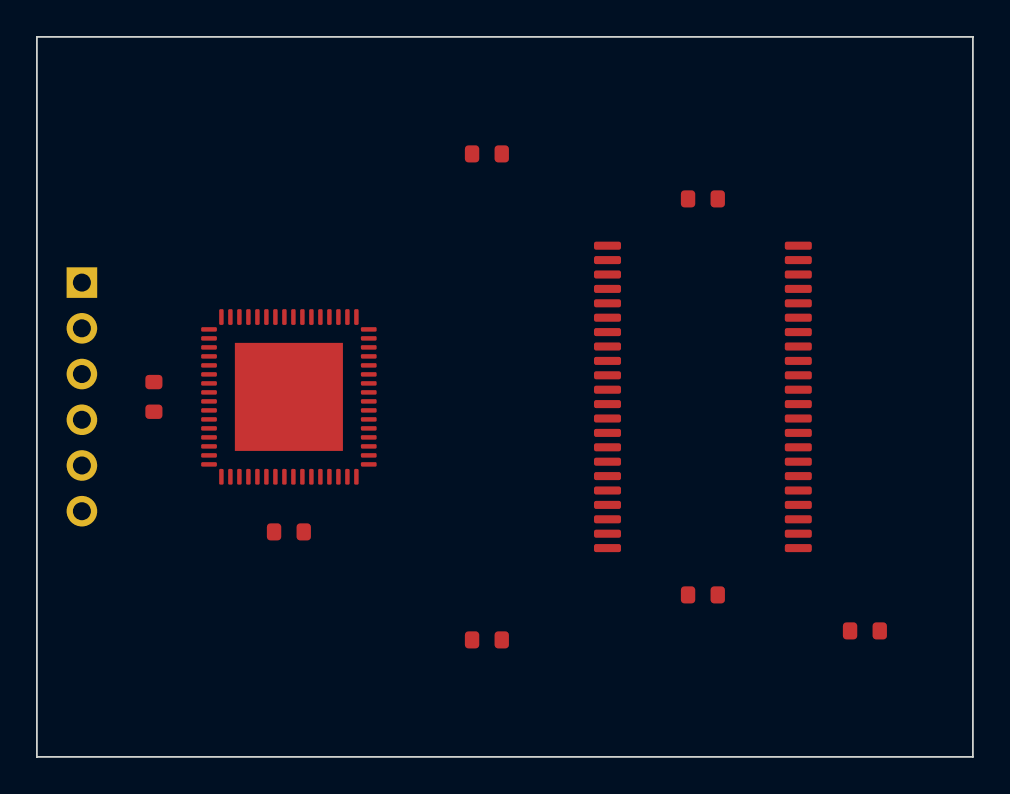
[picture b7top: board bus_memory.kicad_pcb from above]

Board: 4 copper layers, 52.0 x 40.0 mm, 10 parts (0 on the bottom side), 33 nets, no tracks yet.

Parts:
C1, C2, C3, C4: 100n; C_0603
J1: Conn; PinHeader_1x06
R1, R2, R3: 10k; R_0603
U1: MCU; QFN-64
U2: SRAM; TSOP-II-44

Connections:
+3V3: C1.1, C2.1, C3.1, C4.1, J1.5, R1.1, R2.1, R3.1, U1.9, U1.25, U2.11, U2.31
A0: U1.44, U2.5
A1: U1.46, U2.4
A2: U1.45, U2.3
A3: U1.47, U2.2
A4: U1.48, U2.1
A5: U1.49, U2.40
A6: U1.50, U2.39
A7: U1.51, U2.38
A8: U1.53, U2.27
A9: U1.54, U2.26
A10: U1.55, U2.25
A11: U1.56, U2.24
A12: U1.30, U2.21
A13: U1.31, U2.20
A14: U1.32, U2.19
A15: U1.33, U2.18
CE: R1.2, U1.43, U2.6
D0: U1.42, U2.7
D1: U1.41, U2.8
D2: U1.40, U2.9
D3: U1.39, U2.10
D4: U1.38, U2.13
D5: U1.37, U2.14
D6: U1.36, U2.15
D7: U1.35, U2.16
DBG0: J1.1, U1.3
DBG1: J1.2, U1.5
DBG2: J1.3, U1.7
DBG3: J1.4, U1.12
GND: C1.2, C2.2, C3.2, C4.2, J1.6, U1.10, U1.26, U1.65, U2.12, U2.32
OE: R3.2, U1.52, U2.37
WE: R2.2, U1.34, U2.17

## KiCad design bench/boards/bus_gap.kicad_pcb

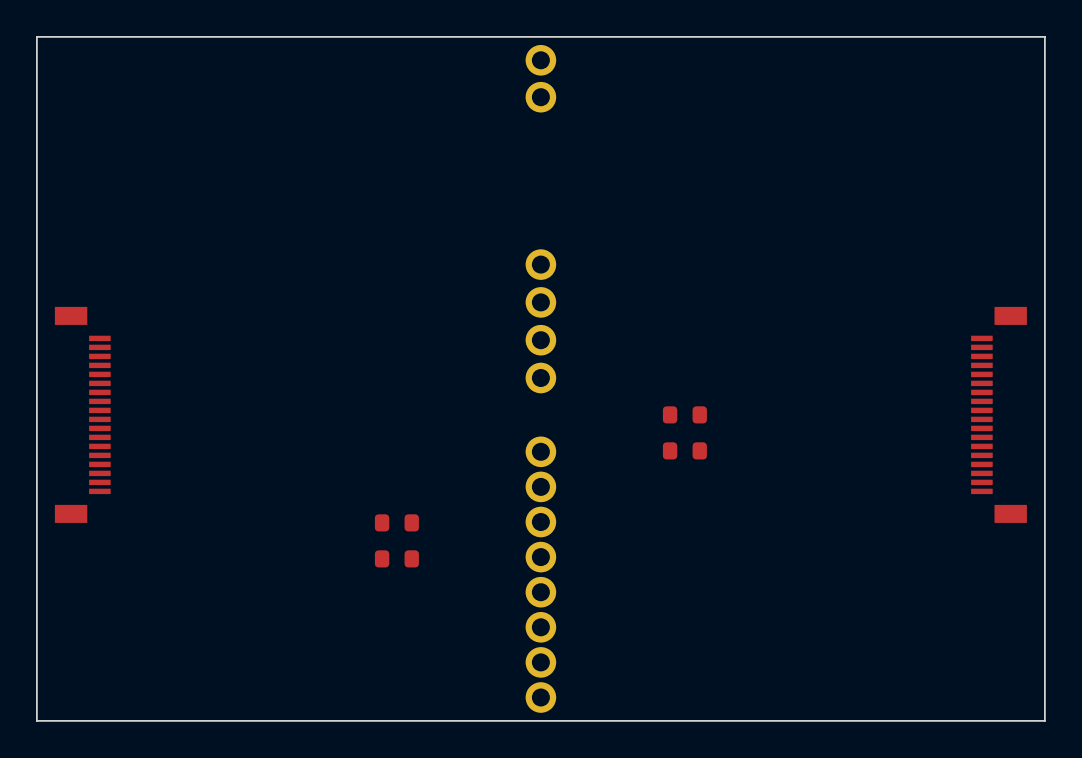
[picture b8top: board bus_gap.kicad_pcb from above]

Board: 2 copper layers, 56.0 x 38.0 mm, 7 parts (0 on the bottom side), 19 nets, no tracks yet.

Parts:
J1, J2: FPC; FPC-18P-0.5mm
R1, R2, R3, R4: 10k; R_0603
W1: NC; Wall_14

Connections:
D0: J1.17, J2.2
D1: J1.16, J2.3
D2: J1.15, J2.4
D3: J1.14, J2.5
D4: J1.13, J2.6
D5: J1.12, J2.7
D6: J1.11, J2.8
D7: J1.10, J2.9
D8: J1.9, J2.10
D9: J1.8, J2.11
D10: J1.7, J2.12
D11: J1.6, J2.13
D12: J1.5, J2.14
D13: J1.4, J2.15
D14: J1.3, J2.16
D15: J1.2, J2.17
GND: J1.1, J1.18, J2.1, J2.18, R1.1, R2.2, R3.1, R4.2
S0: R1.2, R2.1
S1: R3.2, R4.1
